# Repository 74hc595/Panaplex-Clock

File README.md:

# Panaplex Clock

This is a digital clock that uses ["Panaplex" planar gas discharge displays](http://www.tube-tester.com/sites/nixie/trade08-panaplex.htm). Panaplex displays are basically Nixie tubes with a seven-segment cathode arrangement instead of one shaped cathode per digit. And they look *awesome*. The uniform orange glow and lack of gaps between segments make them much more visually appealing than LED displays.

**[Video overview](https://youtu.be/n3AglZmtvWA)**

## Features

- 10-digit display
- Sleek, buttonless enclosure made from laser-cut walnut hardwood and acrylic
- Powered from a 5V USB charger
- Coin cell battery backup keeps time when unplugged
- Two capacitive touch sensors for user input
- Highly accurate oscillator; keeps time within ±2 parts per million (about 1 minute per year)
- 12-hour or 24-hour time display with seconds
- Weekday, month, date, and year display
- Automatic calculation of weekday from month/day/year
- Automatic leap year correction up to 2099
- Automatic daylight saving time correction (US) up to 2099
- Sleep mode: display is normally blanked, and a touch displays the time for 10 seconds before fading out
- Scheduled sleep: for each day of the week, the clock can be configured to be on contiuously, in sleep, or on during one of two configurable time ranges

## Background

"Panaplex" was a trademark of [Burroughs Corporation](http://tmsearch.uspto.gov/bin/showfield?f=doc&state=4810:w635z4.2.1), but on the internet, the term is now used generically to describe planar gas discharge displays made by other manufacturers.

The particular modules used in my clock (the SP-35x series) were introduced by [Sperry's Information Displays Division](https://en.wikipedia.org/wiki/Sperry_Corporation) in the early 1970s. I haven't found an exact date of introduction, but they are listed in this gorgeous [February 1973 Sperry Information Displays Catalog (pdf)](http://www.waynekirkwood.com/images/pdf/Sperry_Information_Displays_Catalog_1973.pdf), which implies they were introduced in 1972 or earlier. Sperry's display division was acquired by [Beckman](https://www.beckman.com/about-us/company-history/company-history-timeline) later in 1973. Babcock acquired the display division from Beckman in [1984](http://www.procureinc.com/manufacturer/Babcock_-_Microsemi/). Babcock was [acquired by Microsemi in 2008](https://www.eetimes.com/document.asp?doc_id=1169534).

These gas discharge displays (also called "plasma displays," though nowadays that term refers to TVs) were used extensively in aviation (as they are readable in bright sunlight) and in many pinball machines starting from the mid-1970s. They are still sold by [Vishay](https://www.vishay.com/displays/plasma/) at exorbitant prices.

## Hardware

I built the clock predominantly out of parts I had on hand. The electronics are constructed on four single-sided PCBs I milled with a desktop CNC machine. Here's a top view:

```
             Display Board              
     ──────────────────────────────     
 Left│                            │Right
 Wing│       ┌───────────┐        │Wing 
Board│       │Logic board│        │Board
     │       └───────────┘        │     
```

- The display board contains the Panaplex displays and the anode drive transistors
- Each "wing board" is mounted at a right angle to the display board and contains a cathode driver chip
- The logic board contains the microcontroller, real-time clock, backup battery, and high voltage power supply

Dave Jones of [EEVblog](eevblog.com) has a great series of videos ([part 1](https://www.youtube.com/watch?v=7uogKucrPks), [part 2](https://www.youtube.com/watch?v=hkbPJONJLfs), [part 3](https://www.youtube.com/watch?v=ggVu_U-CsAk&t=1123s)) where he describes how Nixie tubes can be driven with inexpensive TPIC6B595 open-drain shift registers instead of more expensive/exotic parts designed specifically for high voltage display applications. The [TPIC6B595](http://www.ti.com/product/TPIC6B595) is a cousin of the [74HC595 shift register](https://www.sparkfun.com/products/13699) (and also the namesake of my online handle) with 50V clamping diodes on its eight outputs.

Like Nixie tubes, Panaplex displays require a DC anode voltage of about 160-180 volts to operate. I'm using a [Taylor Electronics 1363](http://www.tayloredge.com/storefront/SmartNixie/PSU/index.html) high voltage supply module to step the 5V input voltage up to about 165-170V.

In addition to requiring a 5V supply, the TPIC6B595 also requires logic high inputs to be at least 4.2V. This meant that I would either have to

- use a microcontroller and real-time clock that could operate from a 5V supply, or
- add a 3.3V regulator and level translation circuitry between the microcontroller and the TPIC6B595s

I decided to go with the former to minimize part count. Looking through the microcontrollers I had on hand, I chose a [PIC16F1508](http://www.microchip.com/wwwproducts/en/PIC16F1508) with 256 bytes of RAM, 4K of ROM, and 18 I/O pins. The [ATtiny461A](http://www.microchip.com/wwwproducts/en/ATtiny461A) was the runner-up, but it only had 15 I/O pins, and the criss-crossed VCC and GND pin arrangement would have made a single-sided board layout difficult. All the ARM chips I had on hand were 3.3V parts, so an 8-bit micro was the only option.

To strike a good balance between pin usage and part count, I ganged the digit anodes together in pairs:

```  
   ┌─────────────┐   
   │   ┌─────┐   │   
┌─┬─┬─┬─┬─┬─┬─┬─┬─┬─┐
│5│4│3│2│1│1│2│3│4│5│
└─┴─┴─┴─┴─┴─┴─┴─┴─┴─┘
 │   │   └─┘   │   │ 
 │   └─────────┘   │ 
 └─────────────────┘ 
```

This arrangement only requires 5 anode drive circuits (10 transistors total and 5 I/O lines). The display is multiplexed by the microcontroller; only 2 digits are ever illuminated at a time, so we need to be able to drive 16 segments at once. For this, I used two TPIC6B595s; one to drive the cathodes of the digits on each half of the display. This led to a compact form factor where the display PCB was no larger than the displays themselves, with each TPIC6B595 on a "wing" board mounted at right angles to the display board.

My favorite real-time clock chip, the [PCF2129AT](https://www.nxp.com/docs/en/data-sheet/PCF2129.pdf), has a recommended 4.2V maximum supply voltage. Rather than push it past its specs, I Amazon Primed a [SparkFun DeadOn RTC breakout board](https://www.sparkfun.com/products/10160). The [DS3234](https://www.maximintegrated.com/en/products/digital/real-time-clocks/DS3234.html) is a highly accurate (±2ppm) clock, but golly gee whiz is it expensive. But, since this was a one-off, and Amazon Prime was the only way I was gonna get a DS3234 within 2 days, I figured it was OK to splurge.

The enclosure design is an homage to the wood-grain Heathkit clocks from the 1970s, like the [GC-1005](http://tubetime.us/index.php/2012/04/). After searching through my parts boxes for some nice buttons and coming up empty-handed, I decided to use capacitive touch pads for user input, which resulted in a very clean design with no protrusions.

## Software

The PIC16F1508 doesn't have any dedicated touch sensing hardware, but I stumbled upon Microchip Application Note [AN1298](http://ww1.microchip.com/downloads/en/AppNotes/01298A.pdf) which describes a technique that uses the built-in analog-to-digital converter and requires no external components. I still don't fully understand how it works (capacitive touch sensing is serious black magic) but it does the job!

Microchip has another app note, [AN1334](http://ww1.microchip.com/downloads/en/AppNotes/00001334B.pdf), that describes a lot of great hardware and software techniques for implementing capacitive touch. By sampling the touch sensor every 64 microseconds and using the slew-rate-limiting algorithm described in that document, I was able to get considerable noise reduction.

When power is first applied, several readings are taken from the two touch sensors to establish a baseline level. It takes 512 samples of a touch sensor to establish whether it is "pressed" or not. If a certain number of those samples deviate sufficiently from the baseline value, the sensor is considered "pressed." Since the touch sensors are read one at a time, the full input state is updated at a rate of 15.26 Hz. Though this figure seems low, I haven't found any issues with responsiveness.

Timer2 drives the display multiplexing, at a rate of 4 kHz. (Each pair of digits is on for 250 microseconds). However, I ran into an issue.

I started out thinking I would strobe the digits sequentially in pairs:

```
. . . . 1 1 . . . .
. . . 2 . . 2 . . .
. . 3 . . . . 3 . .
. 4 . . . . . . 4 .
5 . . . . . . . . 5
. . . . 1 1 . . . .
etc.
```

But I was noticing a [strange blue discharge between neighboring digits](https://pbs.twimg.com/media/DNB2jnqVwAAFHNp.jpg). These blue "streamers" can appear if there is insufficient blanking time between two neighboring digits; the anode with the lower potential will act like a cathode, resulting in a visible blue glow between anodes.

(Interesting aside: where exactly _are_ the anodes? Unlike Nixie tubes, which have visible anode grids in front of the digits, there's nothing like that to be found in Panaplex displays. Well, it turns out that the anodes _are_ in front of the digits, but they're made of [indium tin oxide](https://en.wikipedia.org/wiki/Indium_tin_oxide), which is a _transparent conductor_! How cool is that?)

So, to increase the blanking time between neighboring digits without inserting additional blanking intervals, I strobe the digits in a staggered sequence:

```
. . . . 1 1 . . . .
. . 3 . . . . 3 . .
5 . . . . . . . . 5
. . . 2 . . 2 . . .
. 4 . . . . . . 4 .
. . . . 1 1 . . . .
etc.
```

(No streamers appear between the two central digits because their anodes are tied together and are always on simultaneously.)

Timer0 fires every 64 microseconds, causing a touch sensor to be sampled. After 1024 ticks of Timer0, the input state is updated and one iteration of the main loop is run. As mentioned earlier, this gives the main loop an update rate of 15.26 Hz, which is sufficient for simple animations.

The real-time clock's 1 Hz square wave output is used to tell the PIC when to fetch the new time.

I didn't want to have to manually set the weekday whenever I changed the clock's date. So [Sakamoto's method](https://en.wikipedia.org/wiki/Determination_of_the_day_of_the_week#Sakamoto.27s_methods) is used to determine the day of the week for a given date. By restricting the year to the range 2000-2099 I eliminate the divisions by 100 and 400, which would be expensive as the PIC has no divider. The modulo-7 operation is still required, but I chose to implement it with repeated subtraction rather than use the `%` operator and pull in the large division routines. Plus, the weekday calculation only needs to happen when the user changes the date. The real-time clock takes care of incrementing the weekday at midnight, but has no notion of how weekdays relate to dates.

The table for automatic daylight saving time correction (for the United States only) only requires 1 byte of data per year. For the range of years from 2000-2099, the spring transition can only occur on one of 14 dates, and the fall transition can only occur on one of 13 dates. Thus, all you need to encode daylight saving time data for a year are two 4-bit indexes into a table of month/date pairs.

Since the real-time clock stores its data in [binary-coded decimal format](https://en.wikipedia.org/wiki/Binary-coded_decimal), I try to do as many internal calculations and comparisons in BCD as possible. Converting from BCD to binary representation (i.e. for doing a table lookup) is simple; `(low nibble) + 10*(high nibble)`. The multiplication by 10 can be reduced to left-shift and add operations. Converting from binary to BCD requires division by 10, but the code never actually has to do this.

As for the code itself, it's written in C, and not something I'm particularly proud of. I haven't taken the time to split functions up into logical groups or add comments. The PIC is a nightmare for C, due to its bank-switching scheme and lack of a general-purpose stack. This makes pointer operations (_especially_ function pointer operations) consume considerable ROM space. The 1508's [enhanced mid-range architecture](http://www.microchip.com/stellent/groups/SiteComm_sg/documents/DeviceDoc/en542713.pdf) adds a linear addressing scheme and new instructions for indirect access/jumps, but Microchip's non-FOSS [XC8](http://www.microchip.com/mplab/compilers) is the only compiler that takes advantage of them. The PIC backend for the open-source [SDCC compiler](http://sdcc.sourceforge.net) does not seem to be under active development.

## Operation

Let's call the two touch sensors on top of the clock `L` and `R`. (assuming you're looking at the clock's face.)

### Time display

Normally, the clock displays the time, in the form `HH-MM-SS` (in 24-hour mode) or `HH-MM-SS A`/`HH-MM-SS P` (in 12-hour mode)

At the 26th second of even minutes, the display cycles to show the day of week, month and day for three seconds, then cycles to the full date in `MM-DD-YYYY` format for three seconds, then back to the time display.

Tap `L` or `R` to manually cycle between displays.

Hold `L` to enter the menu (see below).

Hold `R` to turn off the display. The display will fade out. Tap either `L` or `R` to resume normal operation. All timekeeping operates normally when the display is off.

### Menu

The menu is accessed by holding `L` from the time display. Tapping L cycles through various menu items (to be explained in individual sections below):

- Sleep mode on/off/scheduled
- Set time
- Set date
- Set year
- Select 12-hour or 24-hour display
- Automatic daylight saving time correction on/off
- Time separators off/solid/flashing
- Change time separator appearance
- Change date separator appearance
- Set sleep schedule
- Done (tap `R` to exit the menu)

Hold `L` at any time to return to the time display. Tapping `R` either changes the flashing value or enters a submenu.

### Setting the time and date

From the time display, hold `L` to enter the menu. Tap `L` again to advance to the "set time" prompt:

```
SET HH.MM
```

The word `SET` will be flashing. Tap `R` and the hours will flash. Tap or hold `R` to advance the hours. Tap `L` and the minutes will flash. Tap or hold `R` to advance the minutes. Finally, tap `L` one last time to store the new time and reset the seconds to `00`.

At this point, `SET` should be flashing again. Tap `L` to advance to the "set date" prompt:

```
SET MM-DD
```

Tap `R` and the month will flash. Tap or hold `R` to advance the month. Tap `L` and the date will flash. Tap or hold `R` to advance the date. Tapping `L` one last time advances to the "set year" prompt:

```
YEAR YYYY
```

The year should be flashing. Tap or hold `R` to advance the year. Valid years are 2000-2099.

### Selecting 12-hour or 24-hour mode

From the time display, hold `L` to enter the menu. Tap `L` until you arrive at the 12/24-hour prompt:

```
DISP. 12hr  (or)  DISP. 24hr
```

Tap `R` to alternate between 12-hour and 24-hour modes.

### Enabling/disabling daylight saving time correction

From the time display, hold `L` to enter the menu. Tap `L` until you arrive at the daylight saving time prompt:

```
D.S.T. AUTO  (or)  D.S.T. OFF
```

If DST is set to `AUTO` and the current date is currently in daylight saving time, a `+` will illuminate on the left side of the display.

Only US daylight saving time is supported. On the day of the spring transition, the clock will advance `01:59:59 -> 03:00:00`. On the day of the fall transition, the clock will advance `01:59:59 -> 01:00:00`.

**Note:** an ambiguous condition exists when attempting to set the time to `01:00-01:59` on the day of the fall DST transition. The clock does not know if you mean "the hour `01:xx` before the transition" or "the hour `01:xx` after the transition." In this situation, the clock always assumes the former.

### Changing display appearance

The separators ("colons") between hours, minutes, and seconds can be set to either illuminate solidly, flash once per second, or be off entirely.

From the time display, hold `L` to enter the menu. Tap `L` until you arrive at the time separator prompt:

```
SEP. SOLID  (or)  SEP. FLASH  (or)  SEP. OFF
```

Tap `R` to cycle between the options.

Tap `L` again to advance to the time separator style prompt:

```
SEP.STYLE -
```

You have four choices of time separator:

- hyphen `-`
- dot `.`
- pseudo-colon (looks like `=`)
- tall pseudo-colon (top and bottom horizontal segments illuminated)

Tap `R` to cycle between the options.

Tap `L` again to advance to the date separator style prompt:

```
DATESEP. -  (or)  DATESEP. .
```

Tap `R` to select either a hyphen or dot as the separator between month, day, and year.

### Sleep and scheduled sleep

From the time display, hold `L` to enter the menu. The first item allows you to select between three modes:

- `SLEEP OFF`: display always on 24 hours a day
- `SLEEP ON`: display normally off; touch to wake for 10 seconds
- `SLEEP SCH.`: scheduled sleep (customizable per-day asleep/awake time ranges)

Tap `R` to cycle between the options. Additionally, the `+` will illuminate if the clock is currently awake, and the `-` will illuminate if the clock is currently in sleep mode.

To edit the sleep schedule, tap `L` until you arrive at

```
SET SCHED.
```

Tap `R` to enter the schedule submenu:

```
DAYS 1 2
```

The selection `DAYS` will be flashing. Tap `L` to cycle between three selections:

- `DAYS` - select a sleep schedule for each weekday
- `1` - edit Range 1 (see below)
- `2` - edit Range 2

#### Configuring per-day behavior

With `DAYS` flashing, tap `R` to enter

```
Su. _ _ _ _ _ _ _
```

Each character represents a day of the week, Sunday to Saturday. Tap `L` to advance between days, and tap `R` to select an option for each day:

- `_` - display on 24 hours a day
- `1` - display on during the hours of Range 1 and in sleep mode otherwise
- `2` - display on during the hours of Range 2 and in sleep mode otherwise
- `Ξ` - in sleep mode 24 hours a day

Hold `L` to return to the schedule submenu.

#### Editing time ranges

By selecting Range 1 or Range 2 for a given day, the clock can automatically turn the display on and enter sleep at specific times.

From the schedule submenu, tap `L` until either `1` or `2` is flashing, then tap `R` to enter the range editor.

In 24-hour mode, the range editor display looks like

```
1. 09--17
```

In 12-hour mode, the range editor display looks like

```
1. 9A- 5P
```

The first hour should be flashing. This is the time when the display should turn on. Tap or hold `R` to advance the on-hour.

Tap `L` and the second hour should be flashing. This is the time when the clock should go to sleep. Tap or hold `R` to advance the off-hour.

If the on-hour is later than or equal to the off-hour, an apostrophe `'` will appear next to the off-hour:

```
1. 20-03'
```

This means "turn on at 8PM (20:00) and go to sleep at 3AM (03:00) _the next day_."

## Power consupmtion

When the display is active, the clock consumes about 500 mA (2.5 watts). However, there seems to be a large inrush of current when the high voltage supply is turned on; if the power supply can't handle it, the supply voltage may drop low enough to trip the PIC's brown-out reset circuit. This manifests as a delay of about a second when touching to wake from sleep. The PIC is resetting, and the clock always goes through a touch sensor calibration cycle after a reset, which takes about one second.

A high-quality USB power adapter capable of handling at least 1A will prevent this from happening. The Apple 5W Power Adapter (model A1385) works very well. I've seen this happen with cheaper USB adapters that claim to handle 1A.

I have not measured standby current, but my estimate is a few milliamps.

## Conclusion

Total time to project completion was about a month and a half.

Follow me on Twitter for future project updates and random electronics stuff: [@txsector](https://twitter.com/txsector)

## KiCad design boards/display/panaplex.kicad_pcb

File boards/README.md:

# Panaplex Clock Design Files

The clock is built from four PCBs:

- the display board
- two "wing" boards for the cathode drivers
- the microcontroller board

All board designs are single-sided, as they were designed to be milled onto single-sided FR1 using an [Othermill V2](https://support.bantamtools.com/hc/en-us/articles/115001668853-Othermill-V2-). I'm including the board layouts for completeness; I would **not** recommend fabricating them in their current state, even if you have a desktop CNC mill. In the future I may redo the layouts and get double-sided boards professionally fabricated.

 Some notes:

- Traces and surface-mount components are on the back copper layer. (This is the side that gets milled.)
- Through-hole component footprints (displays, headers, etc.) are on the front "copper" layer. (This is the "blank" side with no copper.)
- The front copper layer is used for wire links and is not intended to be fabricated.
- The wing boards are soldered directly to either side of the display board, at right angles.
- No attention has been paid to silkscreen/soldermask layout.
- The boards were designed to be milled with 1/32" and 1/64" flat endmills. Trace width/spacing was set with these conditions in mind.

In hindsight, milled single-sided FR1 boards were not great for this application. The rapid turnaround time was great, but:

- I tried to make the display board millable using only a 1/32" endmill, which resulted in some traces that were too thin and broke during milling.
- The right-angle joints between the wings and the display board are not structurally sound. Without additional reinforcement, the bonding between the copper and the phenolic substrate becomes the weak point.
- It's *very* easy to lift pads and butcher traces when soldering. I had to do considerable rework during the build process. I completely botched the interconnects between the wing boards and the MCU board and wound up soldering kynar wires directly to the IC leads.
- I forgot to add a proper connector on the display board for the high-voltage supply and had to solder a jumper wire directly to the trace.
- Connections from the 5 anode selects to the drive transistors were left out of the display board schematic. Looking at the board layout, you can see five vias to nowhere. These accept an 0.1" header pin.

## Bill of materials

### Display board

- D1: Beckman SP-355 Panaplex 3 1/2-digit display module. (I haven't found any reference to these online; I pulled mine from some old panel meters.)
- D2, D3: Beckman [SP-353](http://www.industrialalchemy.org/articleview.php?item=20) Panaplex 3-digit display module. From eBay.
- D1, D2, and D3 are socketed in [Mill-Max 0566-2-15-15-21-27-10-0 pin receptacles](https://www.mouser.com/Search/ProductDetail.aspx?R=0566-2-15-15-21-27-10-0virtualkey57510000virtualkey575-055621). They are open on both sides to accomodate pins of arbitrary length.
- Q1, Q3, Q5, Q7, Q9: MMBTA92 high-voltage PNP transistors
- Q2, Q4, Q6, Q8, Q10: MMBTA42 high-voltage NPN transistors
- All resistors 1206, 1/4 watt

### Wings

- U1, U2: TPIC6B595DWRG4 power logic 8-bit shift registers
- All resistors 1206, 1/4 watt

### Microcontroller board

- U1: PIC16F1508-I/P
- U2: [SparkFun DeadOn DS3234 breakout board](https://www.sparkfun.com/products/10160) (I used a breakout board because I could get one with free 2-day shipping on Amazon, which wouldn't have been possible if I had ordered the bare DS3234s.)
- J5: [Taylor Electronics 1363](http://www.tayloredge.com/storefront/SmartNixie/PSU/index.html) high voltage power supply since I have a couple on hand. I desoldered the straight dual-row header and replaced it with a right-angle header to make the design more compact.
- C1, R1, R2: resistors and capacitors 1206. All resistors 1/4 watt.
- C2: bodged-in 470uF electrolytic capacitor. Switching on the high-voltage supply can cause the 5V supply to drop for a brief period, which would cause the PIC to brown out.

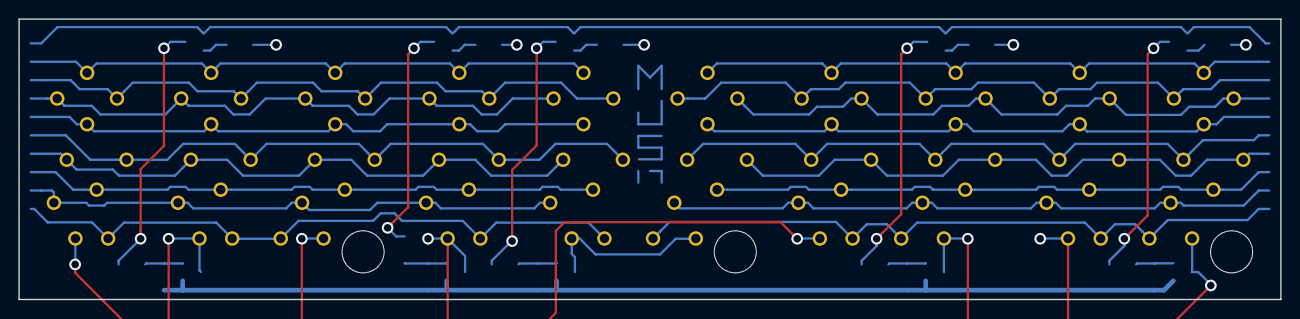
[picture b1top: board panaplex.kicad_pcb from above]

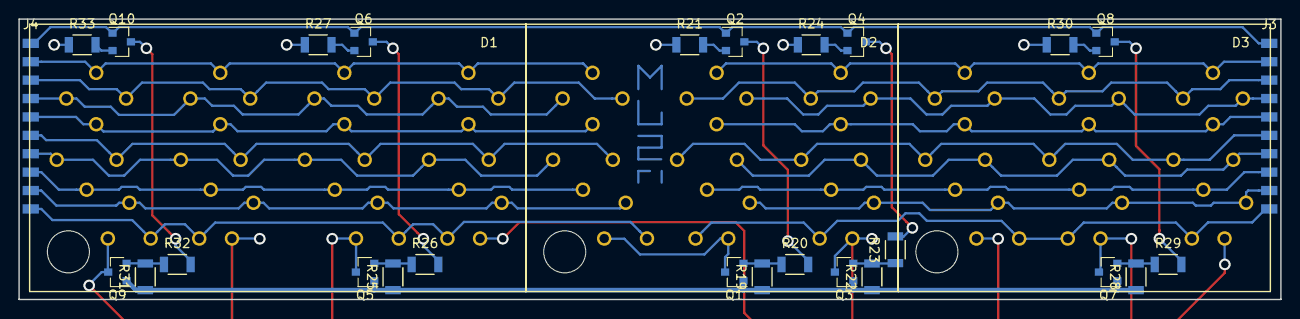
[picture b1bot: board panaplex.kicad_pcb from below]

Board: 2 copper layers, 137.2 x 30.5 mm, 30 parts (30 on the bottom side), 40 nets.

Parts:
D1: SP-355; Panaplex_SP-355_PinSockets
D2, D3: SP-353; Panaplex_SP-353_PinSockets
J3, J4: CONN_01X10; Pads_1x10_Pitch2.00mm_SMD
Q1, Q3, Q5, Q7, Q9: MMBTA92; SOT-23_Flipped
Q2, Q4, Q6, Q8, Q10: MMBTA42; SOT-23_Flipped
R19, R22, R25, R28, R31: 100k; R_1206
R20, R23, R26, R29, R32: 470k; R_1206
R21, R24, R27, R30, R33: 33k; R_1206

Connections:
+170V: Q1.2, Q3.2, Q5.2, Q7.2, Q9.2, R19.1, R22.1, R25.1, R28.1, R31.1
/AN0: D2.B9, D2.C9, Q1.3
/AN1: D1.A9, D2.A9, Q3.3
/AN2: D1.B9, D3.C9, Q5.3
/AN3: D1.C9, D3.B9, Q7.3
/AN4: D1.D9, D3.A9, Q9.3
/K0A: D2.A1, D2.B1, D3.A1, D3.B1, D3.C1, J3.2
/K0B: D2.A2, D2.B2, D3.A2, D3.B2, D3.C2, J3.4
/K0C: D2.A3, D2.B3, D3.A3, D3.B3, D3.C3, J3.7
/K0D: D2.A4, D2.B4, D3.A4, D3.B4, D3.C4, J3.8
/K0E: D2.A5, D2.B5, D3.A5, D3.B5, D3.C5, J3.6
/K0F: D2.A6, D2.B6, D3.A6, D3.B6, D3.C6, J3.3
/K0G: D2.A7, D2.B7, D3.A7, D3.B7, D3.C7, J3.5
/K0P: D2.A8, D2.B8, D3.A8, D3.B8, D3.C8, J3.9
/K1A: D1.A1, D1.B1, D1.C1, D1.D1, D2.C1, J4.2
/K1B: D1.A2, D1.B2, D1.C2, D1.D2, D2.C2, J4.3
/K1C: D1.A3, D1.B3, D1.C3, D1.D3, D2.C3, J4.6
/K1D: D1.A4, D1.B4, D1.C4, D1.D4, D2.C4, J4.8
/K1E: D1.A5, D1.B5, D1.C5, D1.D5, D2.C5, J4.7
/K1F: D1.A6, D1.B6, D1.C6, D1.D6, D2.C6, J4.4
/K1G: D1.A7, D1.B7, D1.C7, D1.D7, D2.C7, J4.5
/K1P: D1.A8, D1.B8, D1.C8, D1.D8, D2.C8, J4.9
/KA0: D2.A10, D2.B10, D3.A10, D3.B10, D3.C10, J3.10
/KA1: D1.A10, D1.B10, D1.C10, D1.D10, D2.C10, J4.10
GND: J3.1, J4.1, Q2.2, Q4.2, Q6.2, Q8.2, Q10.2
unnamed: Q1.1, R19.2, R20.1
unnamed: Q2.1, R21.2
unnamed: Q2.3, R20.2
unnamed: Q3.1, R22.2, R23.1
unnamed: Q4.1, R24.2
unnamed: Q4.3, R23.2
unnamed: Q5.1, R25.2, R26.1
unnamed: Q6.1, R27.2
unnamed: Q6.3, R26.2
unnamed: Q7.1, R28.2, R29.1
unnamed: Q8.1, R30.2
unnamed: Q8.3, R29.2
unnamed: Q9.1, R31.2, R32.1
unnamed: Q10.1, R33.2
unnamed: Q10.3, R32.2

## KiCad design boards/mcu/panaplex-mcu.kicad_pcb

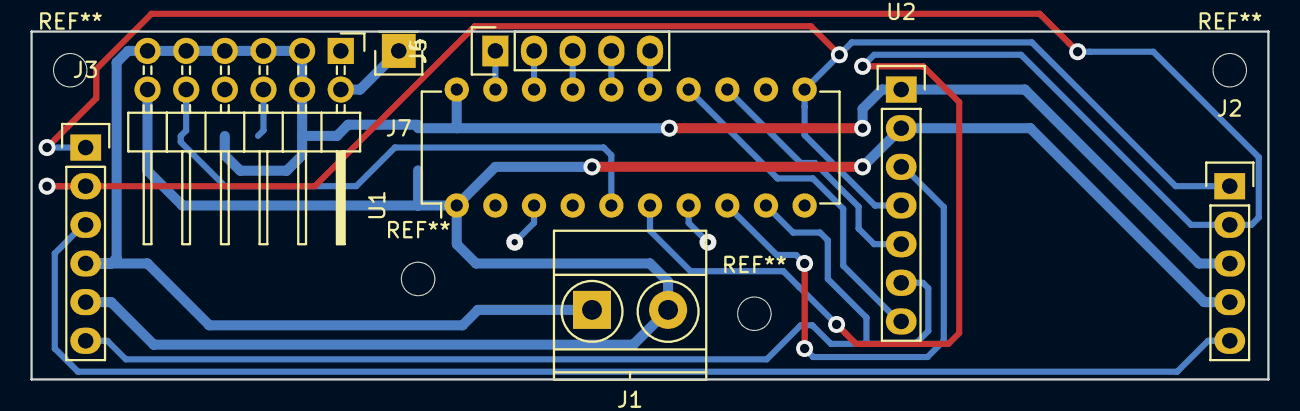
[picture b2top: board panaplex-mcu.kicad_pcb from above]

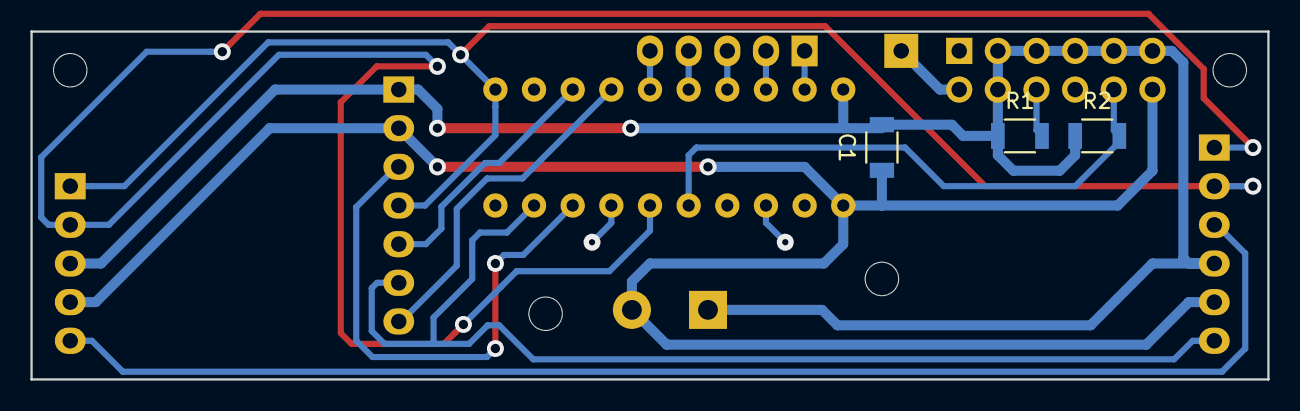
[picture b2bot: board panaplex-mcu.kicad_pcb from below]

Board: 2 copper layers, 81.3 x 22.9 mm, 11 parts (3 on the bottom side), 17 nets.

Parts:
C1: 0.1uF; C_1206
J1: Screw_Terminal_1x02; TerminalBlock_Pheonix_MKDS1.5-2pol
J2: To Right Wing; Pin_Header_Straight_1x05
J3: To Left Wing; Pin_Header_Straight_1x06
J4: Anode Selects; Pin_Header_Straight_1x05
J5: Tayloredge 1363; Pin_Header_Angled_2x06
J7: HV Out; Pin_Header_Straight_1x01
R1: 68k; R_1206
R2: 100k; R_1206
U1: PIC16F1508-I/P; DIP-20_W7.62mm
U2: SparkFun DeadOn RTC (DS3234); Pin_Header_Straight_1x07

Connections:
/ANSEL0: J4.1, U1.19
/ANSEL1: J4.2, U1.18
/ANSEL2: J4.3, U1.17
/ANSEL3: J4.4, U1.16
/ANSEL4: J4.5, U1.15
/DCASC: J2.5, J3.3
/HV: J5.2, J7.1
/HV_EN: J5.10, R2.2, U1.5
/LATCH: J2.2, J3.1, U1.6
/MISO: U1.13, U2.5
/MOSI: J3.6, U1.9, U2.6
/SCK: J2.1, J3.2, U1.11, U2.4
/SQW: U1.8, U2.3
/~RTC_SS: U1.14, U2.7
GND: C1.2, J1.1, J2.3, J3.4, J5.3, J5.4, J5.5, J5.7, J5.9, J5.11, R1.1, R2.1, U1.20, U2.1
unnamed: J5.6, R1.2
VCC: C1.1, J1.2, J2.4, J3.5, J5.12, U1.1, U2.2

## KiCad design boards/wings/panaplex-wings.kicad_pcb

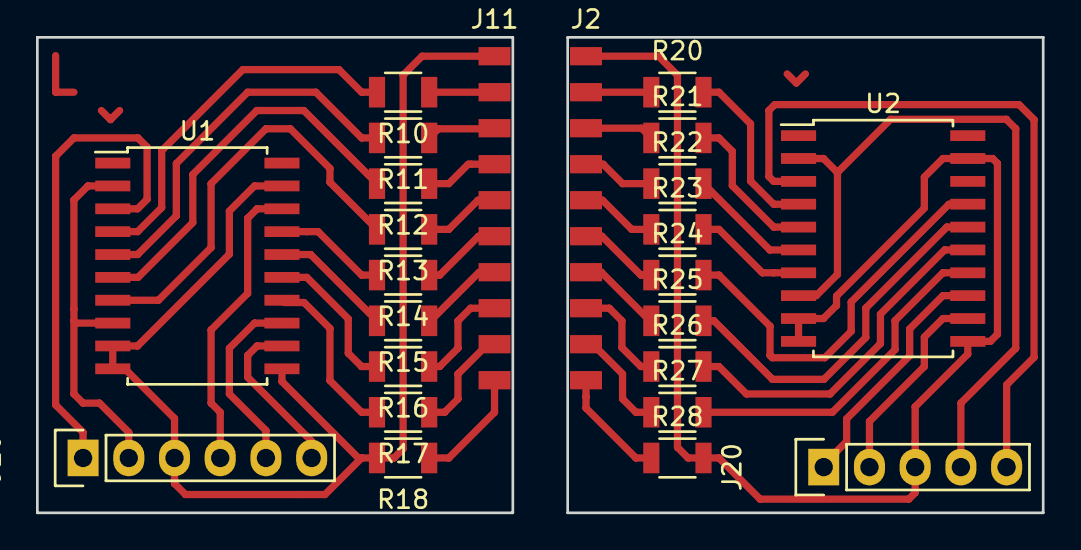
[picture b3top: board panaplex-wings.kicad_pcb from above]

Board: 2 copper layers, 55.9 x 26.4 mm, 24 parts (0 on the bottom side), 43 nets.

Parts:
J2, J11: CONN_01X10; Pads_1x10_Pitch2.00mm_SMD
J10: CONN_01X06; Pin_Header_Straight_1x06
J20: CONN_01X05; Pin_Header_Straight_1x05
R10, R11, R12, R13, R14, R15, R16, R20, R21, R22, R23, R24, R25, R26: 22k; R_1206
R17, R27: 220k; R_1206
R18, R28: 330k; R_1206
U1, U2: TPIC6B595; SOIC-20W_7.5x12.8mm_Pitch1.27mm

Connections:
/K0A: R10.2, U1.4
/K0B: R12.2, U1.6
/K0C: R15.2, U1.16
/K0D: R16.2, U1.15
/K0E: R14.2, U1.17
/K0F: R11.2, U1.5
/K0G: R13.2, U1.7
/K0P: R17.2, U1.14
/K1A: R20.2, U2.4
/K1B: R22.2, U2.6
/K1C: R25.2, U2.16
/K1D: R26.2, U2.15
/K1E: R24.2, U2.17
/K1F: R21.2, U2.5
/K1G: R23.2, U2.7
/K1P: R27.2, U2.14
GND: J2.1, J10.3, J11.1, J20.3, R18.2, R28.2, U1.9, U1.10, U1.11, U1.19, U2.9, U2.10, U2.11, U2.19
unnamed: J2.2, R20.1
unnamed: J2.3, R21.1
unnamed: J2.4, R22.1
unnamed: J2.5, R23.1
unnamed: J2.6, R24.1
unnamed: J2.7, R25.1
unnamed: J2.8, R26.1
unnamed: J2.9, R27.1
unnamed: J2.10, R28.1
unnamed: J10.1, U1.3
unnamed: J10.4, U1.18
unnamed: J10.5, U1.13
unnamed: J10.6, U1.12
unnamed: J11.2, R10.1
unnamed: J11.3, R11.1
unnamed: J11.4, R12.1
unnamed: J11.5, R13.1
unnamed: J11.6, R14.1
unnamed: J11.7, R15.1
unnamed: J11.8, R16.1
unnamed: J11.9, R17.1
unnamed: J11.10, R18.1
unnamed: J20.1, U2.13
unnamed: J20.2, U2.12
unnamed: J20.5, U2.3
VCC: J10.2, J20.4, U1.2, U1.8, U2.2, U2.8

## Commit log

2017-11-30 Add image to readme
2017-11-30 readme tweaks
2017-11-30 more readme tweaks
2017-12-01 talk about power consumption
2017-12-01 watts!
